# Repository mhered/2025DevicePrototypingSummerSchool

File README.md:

# 2025 Device Prototyping Summer School
My notes and exercises from 2025 Device Prototyping Summer School

* [Day 1](./Day_1.md)
* [Day 2](./Day_2.md)
* [Day 3](./Day_3.md)
* [Day 4](./Day_4.md)

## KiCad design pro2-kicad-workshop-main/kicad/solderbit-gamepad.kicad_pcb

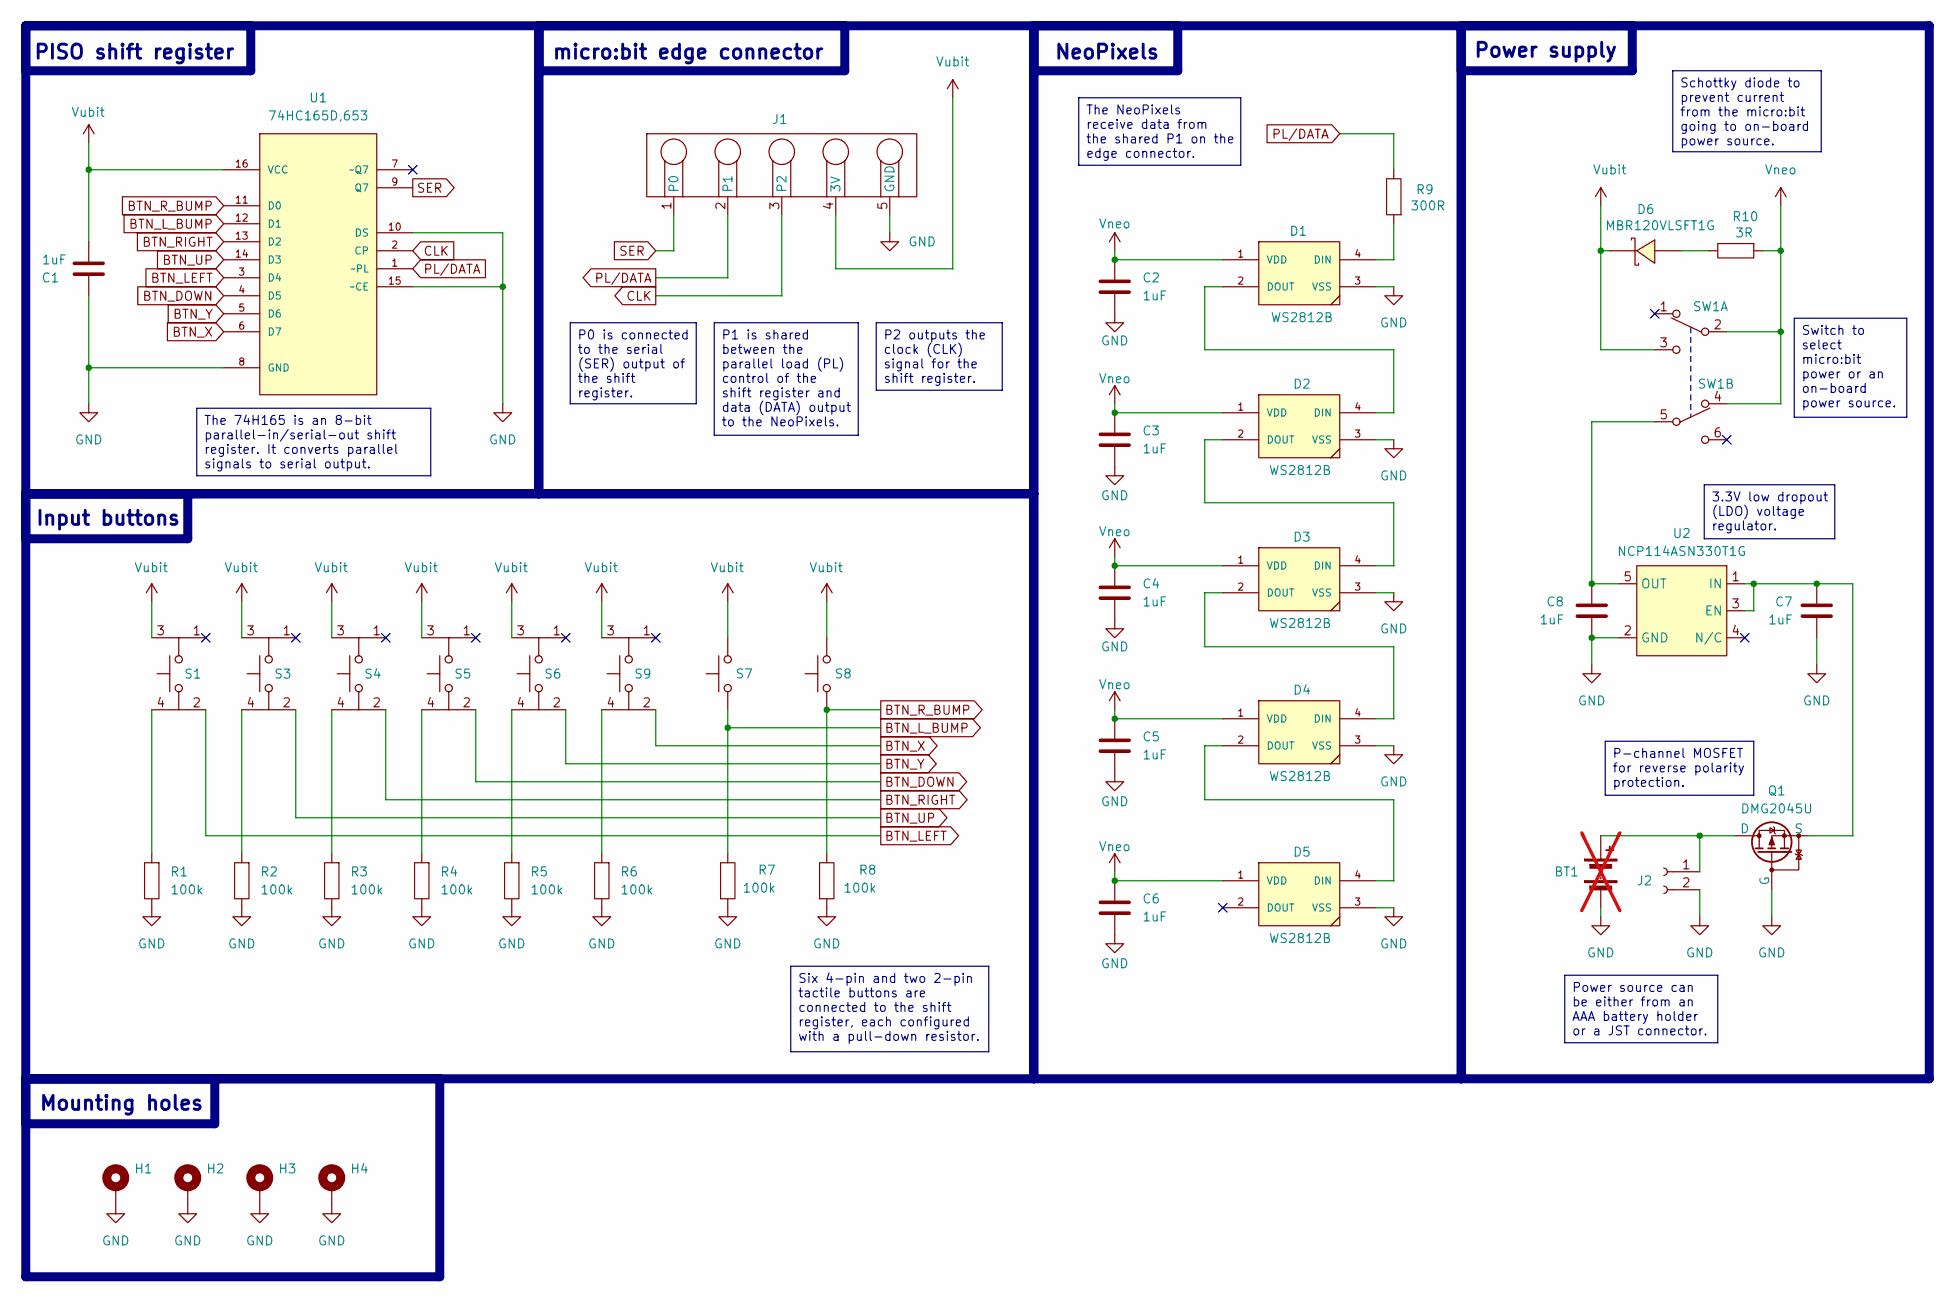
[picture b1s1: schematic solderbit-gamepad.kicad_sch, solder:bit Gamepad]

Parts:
BT1: BH-AAA-B5AA001; Battery_Holder; LCSC Part C964881; not fitted
C1, C2, C3, C4, C5, C6, C7, C8: 1uF; 1206_Capacitor; LCSC Part C1848
D1: WS2812B; NeoPixel_WS2812B; LCSC Part C2843785
D2, D3, D4, D5: WS2812B; NeoPixel_WS2812B
D6: MBR120VLSFT1G; SOD-123FL; LCSC Part C223608
H1, H2, H3, H4: MountingHole_Pad
J1: Microbit_Edge_Connector
J2: S2B-PH-SM4-TB(LF)(SN); JST_PH_S2B-PH-SM4-TB; LCSC Part C295747
Q1: DMG2045U; TSOT-23; LCSC Part C459541
R1, R2, R3, R4, R5, R6, R7, R8: 100k; 1206_Resistor; LCSC Part C17900
R9: 300R; 1206_Resistor; LCSC Part C17887
R10: 3R; 1206_Resistor; LCSC Part C17939
S1: KH-6X6X6H-STM; Tactile_Switch; LCSC Part C2837532
S3, S4, S5, S6, S9: TS-1002S-AR06026; Tactile_Switch
S7: TS-1037-A4B3-D2; Tactile_Switch_Left_90_Degrees; LCSC Part C499324
S8: TS-1037-A4B3-D2; Tactile_Switch_Right_90_Degrees; LCSC Part C499324
SW1: MST22D18G2 125; Sliding_Switch_DPDT; LCSC Part C2906280
U1: 74HC165D,653; Shift_Register_74HC165D; LCSC Part C5613
U2: NCP114ASN330T1G; TSOP-5; LCSC Part C457666

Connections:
BTN_DOWN: S5.2, U1.4 (D5)
BTN_LEFT: S1.2, U1.3 (D4)
BTN_L_BUMP: R7.2, S7.2, U1.12 (D1)
BTN_RIGHT: S4.2, U1.13 (D2)
BTN_R_BUMP: R8.2, S8.2, U1.11 (D0)
BTN_UP: S3.2, U1.14 (D3)
BTN_X: S9.2, U1.6 (D7)
BTN_Y: S6.2, U1.5 (D6)
CLK: J1.3 (P2), U1.2 (CP)
GND: BT1.2 (-), C1.1, C2.2, C3.2, C4.2, C5.2, C6.2, C7.2, C8.2, D1.3 (VSS), D2.3 (VSS), D3.3 (VSS), D4.3 (VSS), D5.3 (VSS), H1.1, H2.1, H3.1, H4.1, J1.5 (GND), J2.2, Q1.1 (G), R1.2, R2.2, R3.2, R4.2, R5.2, R6.2, R7.1, R8.1, U1.8 (GND), U1.10 (DS), U1.15 (~CE), U2.2 (GND)
unnamed: BT1.1 (+), J2.1, Q1.3 (D)
unnamed: D1.4 (DIN), R9.1
unnamed: D1.2 (DOUT), D2.4 (DIN)
unnamed: D2.2 (DOUT), D3.4 (DIN)
unnamed: D3.2 (DOUT), D4.4 (DIN)
unnamed: D4.2 (DOUT), D5.4 (DIN)
unnamed: D6.2, R10.2
unnamed: C7.1, Q1.2 (S), U2.1 (IN), U2.3 (EN)
unnamed: R1.1, S1.4
unnamed: R2.1, S3.4
unnamed: R3.1, S4.4
unnamed: R4.1, S5.4
unnamed: R5.1, S6.4
unnamed: R6.1, S9.4
unnamed: C8.1, SW1.5 (B), U2.5 (OUT)
PL/DATA: J1.2 (P1), R9.2, U1.1 (~PL)
SER: J1.1 (P0), U1.9 (Q7)
Vneo: C2.1, C3.1, C4.1, C5.1, C6.1, D1.1 (VDD), D2.1 (VDD), D3.1 (VDD), D4.1 (VDD), D5.1 (VDD), R10.1, SW1.2 (B), SW1.4 (A)
Vubit: C1.2, D6.1, J1.4 (3V), S1.3, S3.3, S4.3, S5.3, S6.3, S7.1, S8.1, S9.3, SW1.3 (C), U1.16 (VCC)

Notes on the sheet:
NeoPixels
Input buttons
Power supply
micro:bit edge connector
Mounting holes
PISO shift register
P0 is connected to the serial (SER) output of the shift register.
P2 outputs the clock (CLK) signal for the shift register.
Schottky diode to prevent current from the micro:bit going to on-board power source.
P1 is shared between the parallel load (PL) control of the shift register and data (DATA) output to the NeoPixels.
Switch to select micro:bit power or an on-board power source.
3.3V low dropout (LDO) voltage regulator.
The 74H165 is an 8-bit parallel-in/serial-out shift register. It converts parallel signals to serial output.
P-channel MOSFET for reverse polarity protection.
Six 4-pin and two 2-pin tactile buttons are connected to the shift register, each configured with a pull-down resistor.
The NeoPixels receive data from the shared P1 on the edge connector.
Power source can be either from an AAA battery holder or a JST connector.

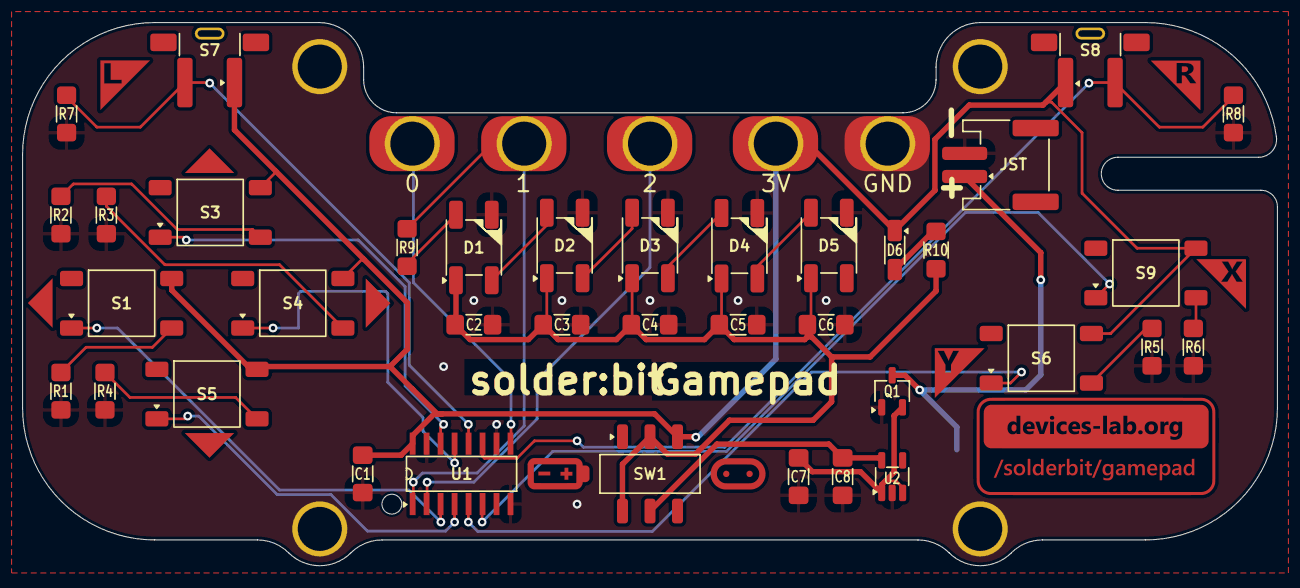
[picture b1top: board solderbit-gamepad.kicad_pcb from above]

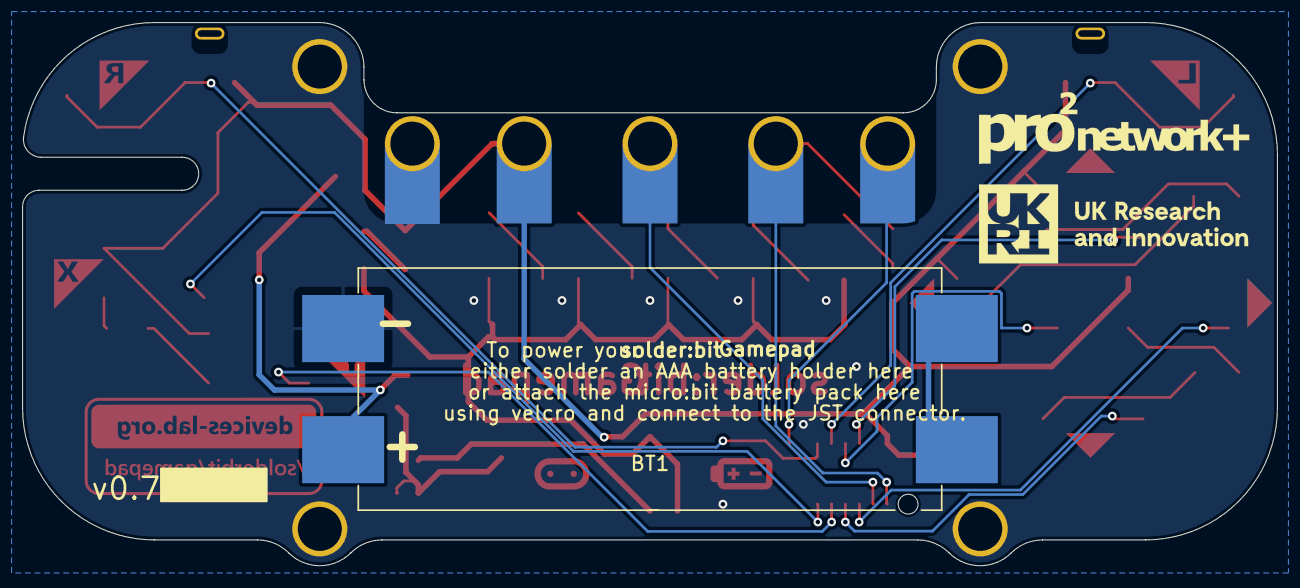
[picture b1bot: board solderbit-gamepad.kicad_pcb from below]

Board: 2 copper layers, 114.0 x 49.3 mm, 54 parts (3 on the bottom side), 29 nets.

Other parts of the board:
G1: Devices-Lab_Logo_H9mm
G4: UKRI_Logo
Ref**: Val**; Button_Label_Y
Ref**#2, Ref**#3, Ref**#4, Ref**#7: Val**; Button_Label_Arrow
Ref**#5: Val**; Button_Label_L
Ref**#6: Val**; Button_Label_X
Ref**#8: Val**; Button_Label_R
Ref**#9: Val**; Pro2_Logo

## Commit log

2025-07-15 Notes first session
2025-07-15 Gamepad tutorial
2025-07-16 CAD workshop Initial commit
2025-07-16 Add CAD tutorial notes
2025-07-16 Add link to file
2025-07-17 Organize notes by day
2025-07-18 Day 3 notes - tidy up, add notes from chat group
2025-07-18 Day 4 - before lunch notes
2025-07-18 Add links to notes
2025-09-18 minor fixes to notes
